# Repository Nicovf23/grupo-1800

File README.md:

# grupo-DON JULIO 
Proyecto Carrito Don Julio
El proyecto Carrito Don Julio consiste en el diseño y desarrollo de un vehículo eléctrico a escala, controlado por radio (RC), orientado al automodelismo de competición en pista para adultos. El objetivo es construir un vehículo desde cero, con un diseño enfocado en el alto rendimiento, la precisión de conducción y las exigencias técnicas de las carreras RC.
El proyecto contempla el diseño y fabricación de un chasis propio, la integración de un sistema de propulsión 100 % eléctrico, el desarrollo de circuitos electrónicos con componentes SMD (Surface-Mount Device) y la implementación de sistemas de control. Cada elemento será diseñado y seleccionado considerando factores como la velocidad, la aceleración, la estabilidad, la distribución del peso y la eficiencia energética.
Para el diseño y desarrollo se utilizarán herramientas especializadas como FreeCAD, para el modelado tridimensional del chasis y sus componentes mecánicos; KiCad, para el diseño de esquemáticos y placas de circuito impreso; Qucs-S, para la simulación y el análisis de circuitos electrónicos; y OpenModelica, para el modelado y la simulación de sistemas dinámicos.
El enfoque principal será desarrollar un vehículo competitivo para carreras en circuitos de pista, aplicando principios de ingeniería mecánica, electrónica, programación y microcontroladores. Se buscará optimizar cada componente para obtener un equilibrio entre potencia, control, estabilidad y rendimiento, mediante un proceso continuo de diseño, fabricación, pruebas y ajustes.

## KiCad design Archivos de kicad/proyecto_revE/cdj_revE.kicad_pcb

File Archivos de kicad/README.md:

# Carrito Don Julio: placa principal (KiCad)

## Revisión E (nueva, 26-11-2026): PRELIMINAR

> ⚠️ **REV E EN DESARROLLO.** Esquemático completo (ERC: 0 errores). PCB colocada y casi ruteada: DRC 0 errores, **73 conexiones sin rutear** todavía. **No mandar a fabricar.**

| | |
|---|---|
| Microcontrolador | **ESP32-S3RH2 soldado** (QFN56) + flash W25Q128JV 16 MB + cristal 40 MHz + antena U.FL |
| Alimentación | 6S → **LMR36510** (5.42 V) → OR con USB → **AP63203** (3.3 V) |
| Programación | USB-C de datos propio (el otro USB-C sigue siendo solo de carga) |
| Seguridad | Failsafe por hardware (monoestable 74LVC1G123 + interruptor de armado) |
| PCB | 125 × 95 mm, 4 capas JLC04161H-7628, In1 = GND sólido |
| Herramienta | **KiCad 10** (no abre en KiCad 9) |

| Carpeta | Contenido |
|---|---|
| `proyecto_revE/` | Proyecto KiCad 10: abrir `cdj_revE.kicad_pro` |
| `documentacion_revE/` | Esquemático PDF, BOM, GPIO, cálculos, auditoría, plan de pruebas, ERC/DRC, imágenes |
| `fabricacion_revE_PRELIMINAR/` | Gerbers, taladros, BOM, CPL, STEP. **Preliminares, no fabricar** |
| `../Documentación/Informe técnico Carrito Don Julio (rev E).pdf` | Informe completo para explicar y entregar |

La rev D (abajo) se conserva como respaldo.

---

## Revisión D

> ⚠️ **ESTADO: EN DESARROLLO. NO ES UNA VERSIÓN DE PRODUCCIÓN.**
> El ruteo está completo (DRC: 0 errores, 0 conexiones sin rutear), pero no mandar a fabricar todavía: faltan verificaciones físicas y una revisión del diseño (ver [AUDITORIA.md](AUDITORIA.md)).

**Revisión:** D, ruteo 3 (11 de noviembre de 2026)
**Herramienta:** KiCad 9.0
**Vehículo:** RC 1:7, 4WD, batería LiPo 6S (22.2 V nominal / 25.2 V cargada)

## Qué hace esta placa

| Bloque | Componentes principales |
|---|---|
| Microcontrolador | ESP32 DevKit V1 (DOIT, 30 pines) en zócalo |
| Sensor de movimiento | IMU LSM6DSL (I2C, dirección 0x6A) |
| Carga de batería por USB-C | CH224K (pide 20 V por PD) → BQ25756 (buck-boost 6S) |
| Monitoreo y balanceo de celdas | BQ76930 (6 celdas, por el cable de balanceo) |
| Alimentación 3.3 V | AP63203WU (componente recomendado por el profesor) |
| Luces | 2× BTS723GW (4 canales con diagnóstico) |
| Radio control | Entradas PWM ×3 + serie (CRSF/SBUS/iBUS), protegidas |
| Salidas | ESC y servo con buffer y habilitación |
| Protección | ESD5Z3.3T, SMF24CA/SMF26CA, SMF3.3, MBRA340T, fusible |

## Estructura de la carpeta

| Carpeta | Contenido |
|---|---|
| `proyecto_revD/` | Proyecto KiCad editable: esquemático, PCB, librería propia `CDJ` (símbolos y huellas) |
| `fabricacion_PRELIMINAR/` | Gerbers, taladros, BOM, posiciones (CPL) y modelo STEP. **Preliminares, no fabricar** |
| `documentacion/` | Esquemático en PDF, vista 3D, BOM clasificada (A/B/C), mapa de pines del DevKit, instrucciones y `EXPLICACION_PLACA.md` (qué hace cada componente y cada parte del PCB) |
| `reportes/` | Informes ERC, DRC y verificación de la netlist |
| `AUDITORIA.md` | Qué está verificado, qué no, y qué falta para producción |
| `NOTAS_DISENO.md` | Decisiones de diseño, supuestos y cálculos |

## Cómo abrir

1. Abrir `proyecto_revD/cdj_revD.kicad_pro` con KiCad 9.
2. La librería `CDJ` se carga sola desde la carpeta del proyecto (`sym-lib-table` y `fp-lib-table`).

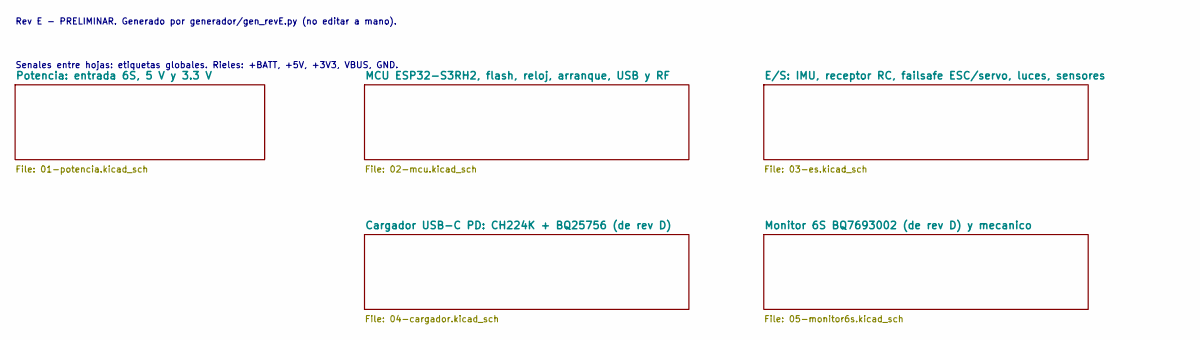
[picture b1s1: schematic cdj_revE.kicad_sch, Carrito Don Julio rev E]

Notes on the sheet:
Senales entre hojas: etiquetas globales. Rieles: +BATT, +5V, +3V3, VBUS, GND.
Rev E - PRELIMINAR. Generado por generador/gen_revE.py (no editar a mano).

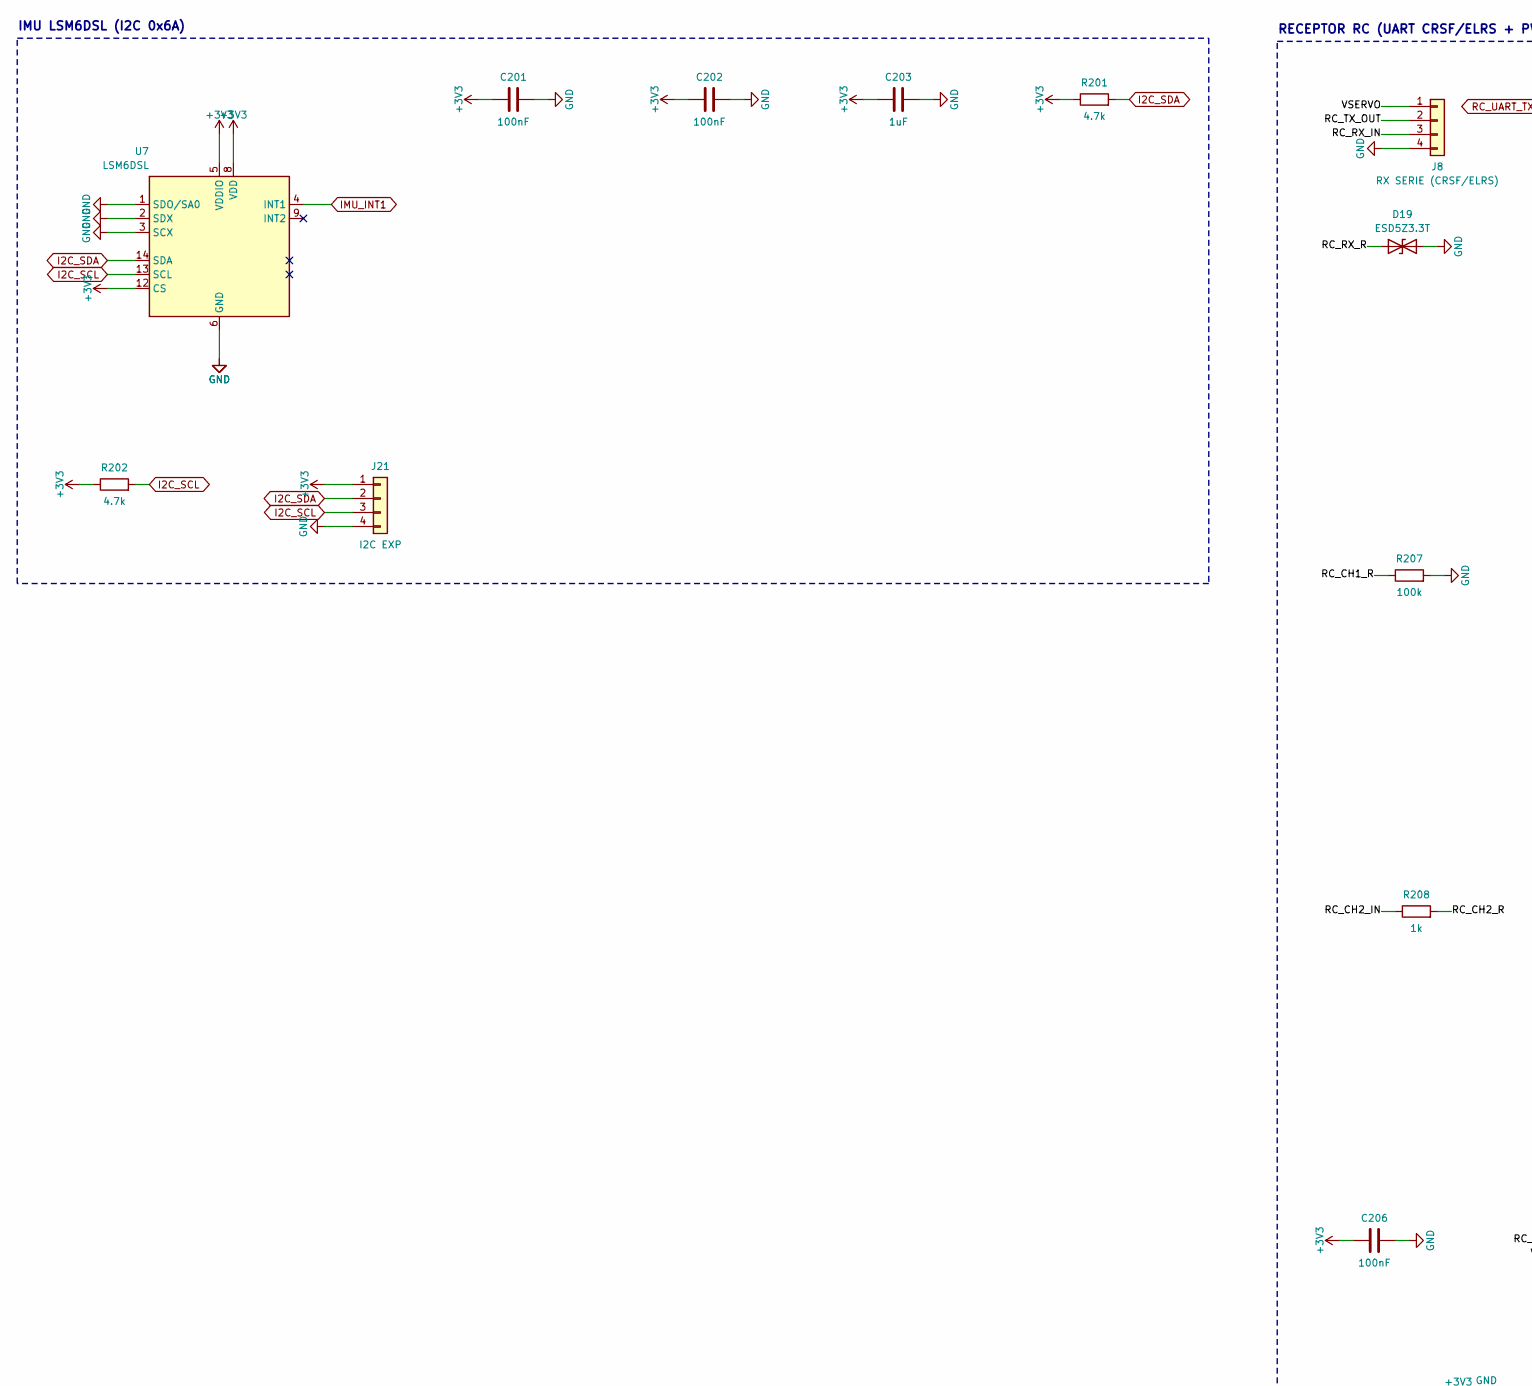
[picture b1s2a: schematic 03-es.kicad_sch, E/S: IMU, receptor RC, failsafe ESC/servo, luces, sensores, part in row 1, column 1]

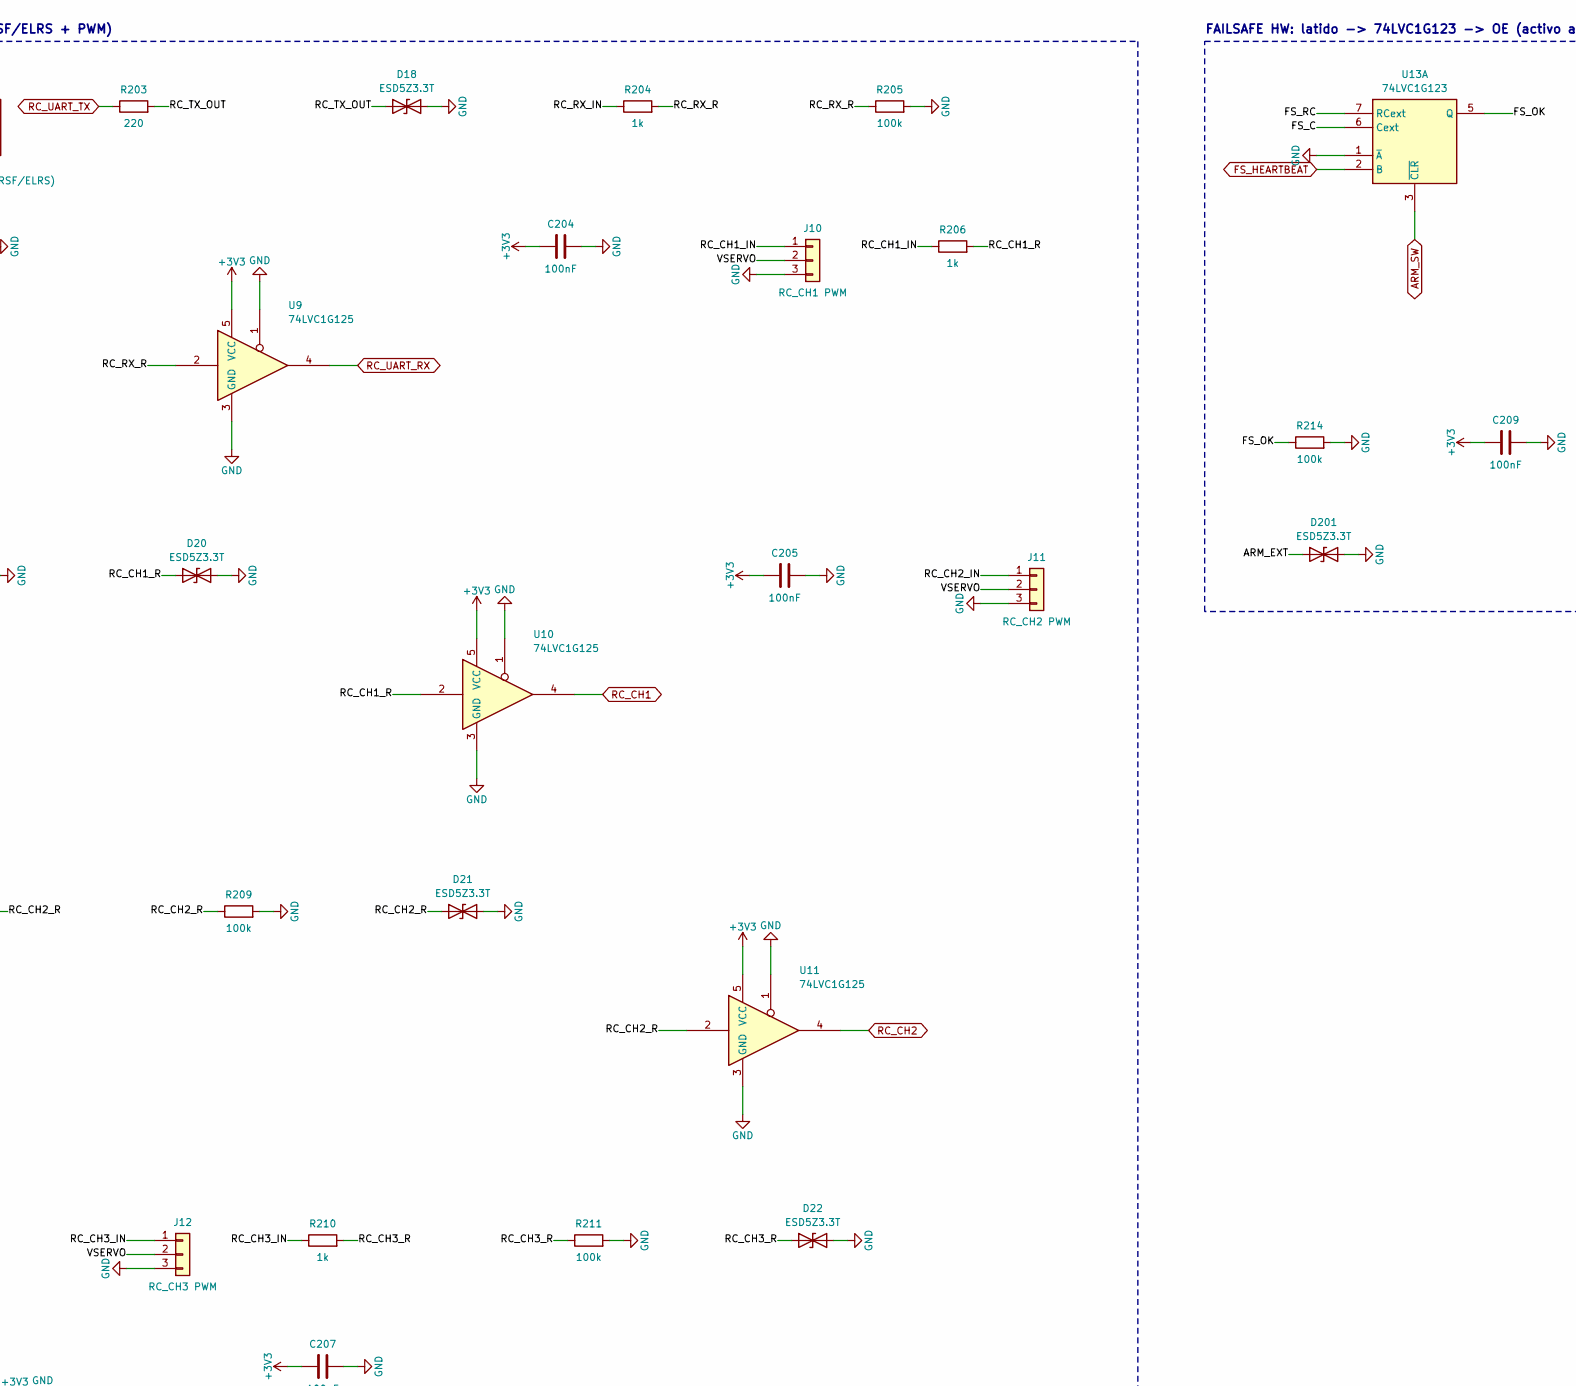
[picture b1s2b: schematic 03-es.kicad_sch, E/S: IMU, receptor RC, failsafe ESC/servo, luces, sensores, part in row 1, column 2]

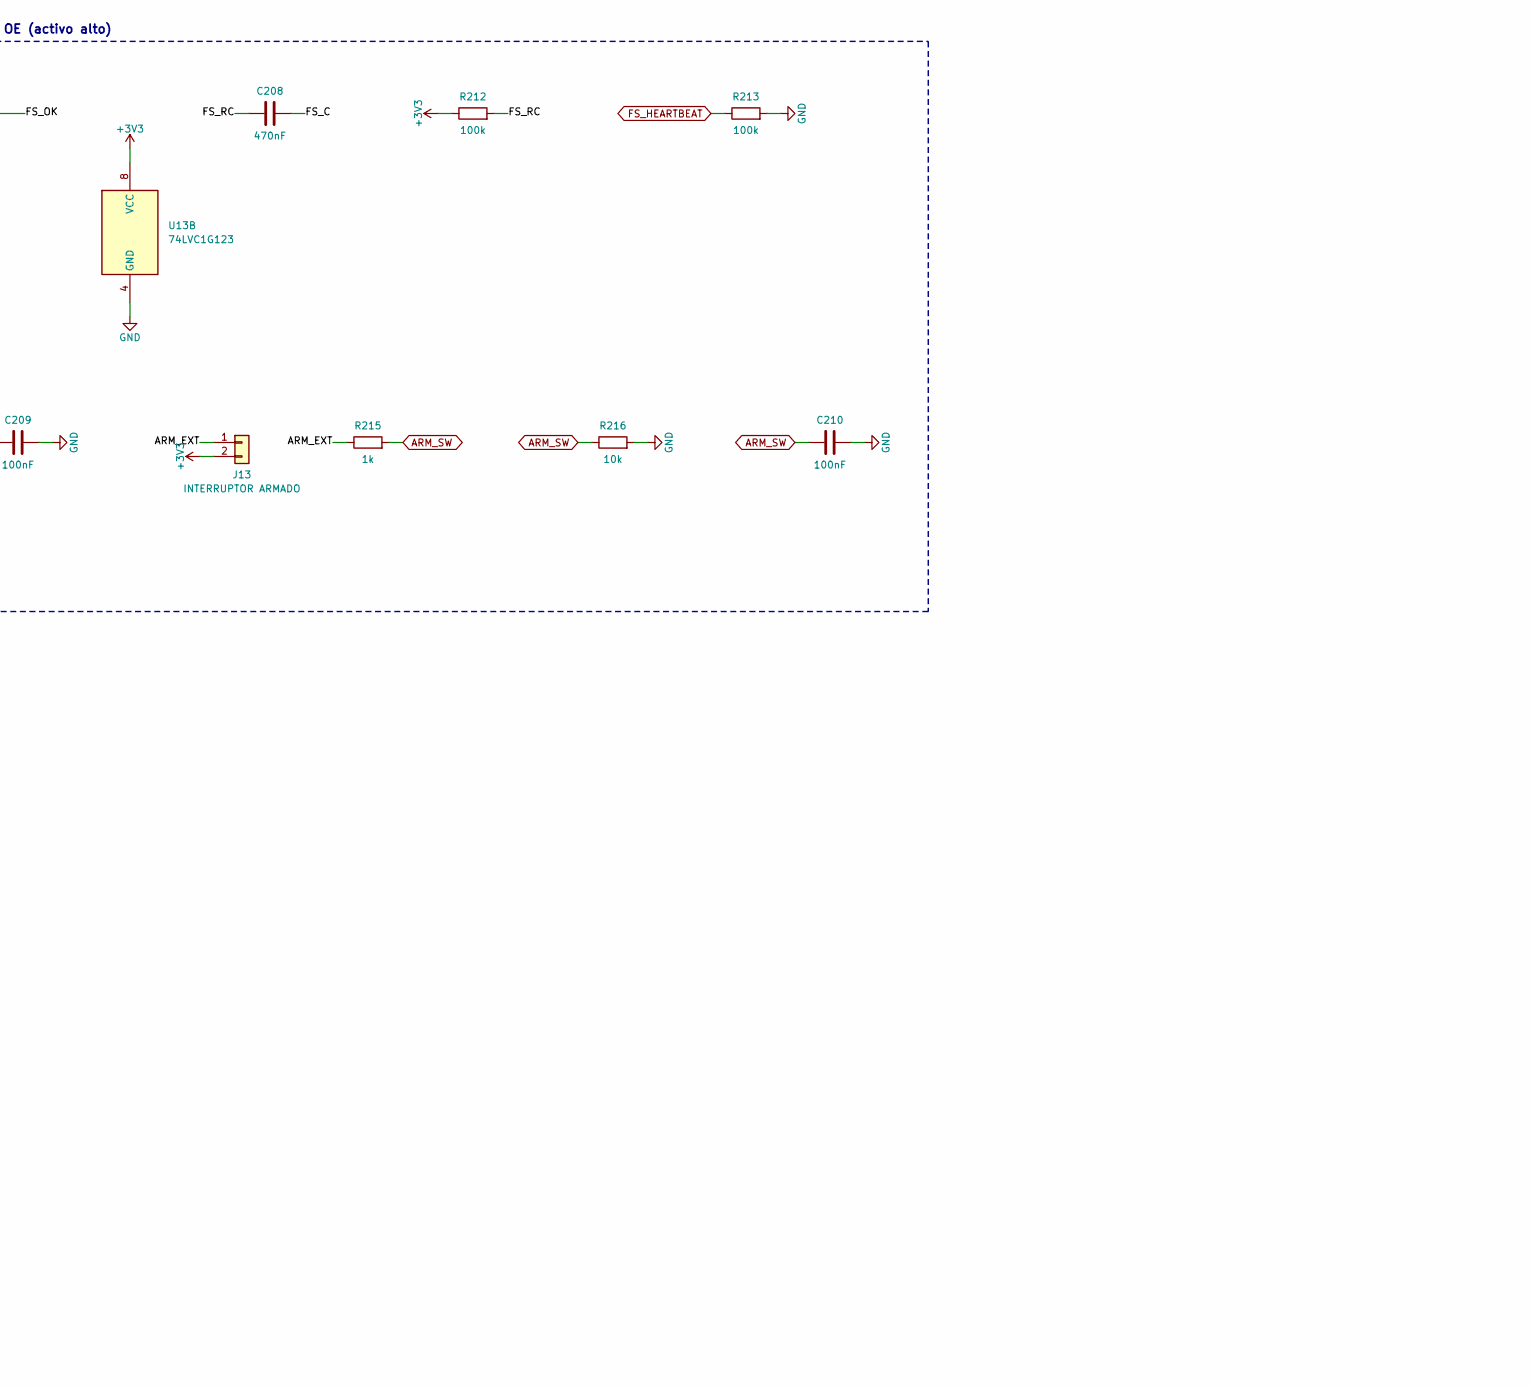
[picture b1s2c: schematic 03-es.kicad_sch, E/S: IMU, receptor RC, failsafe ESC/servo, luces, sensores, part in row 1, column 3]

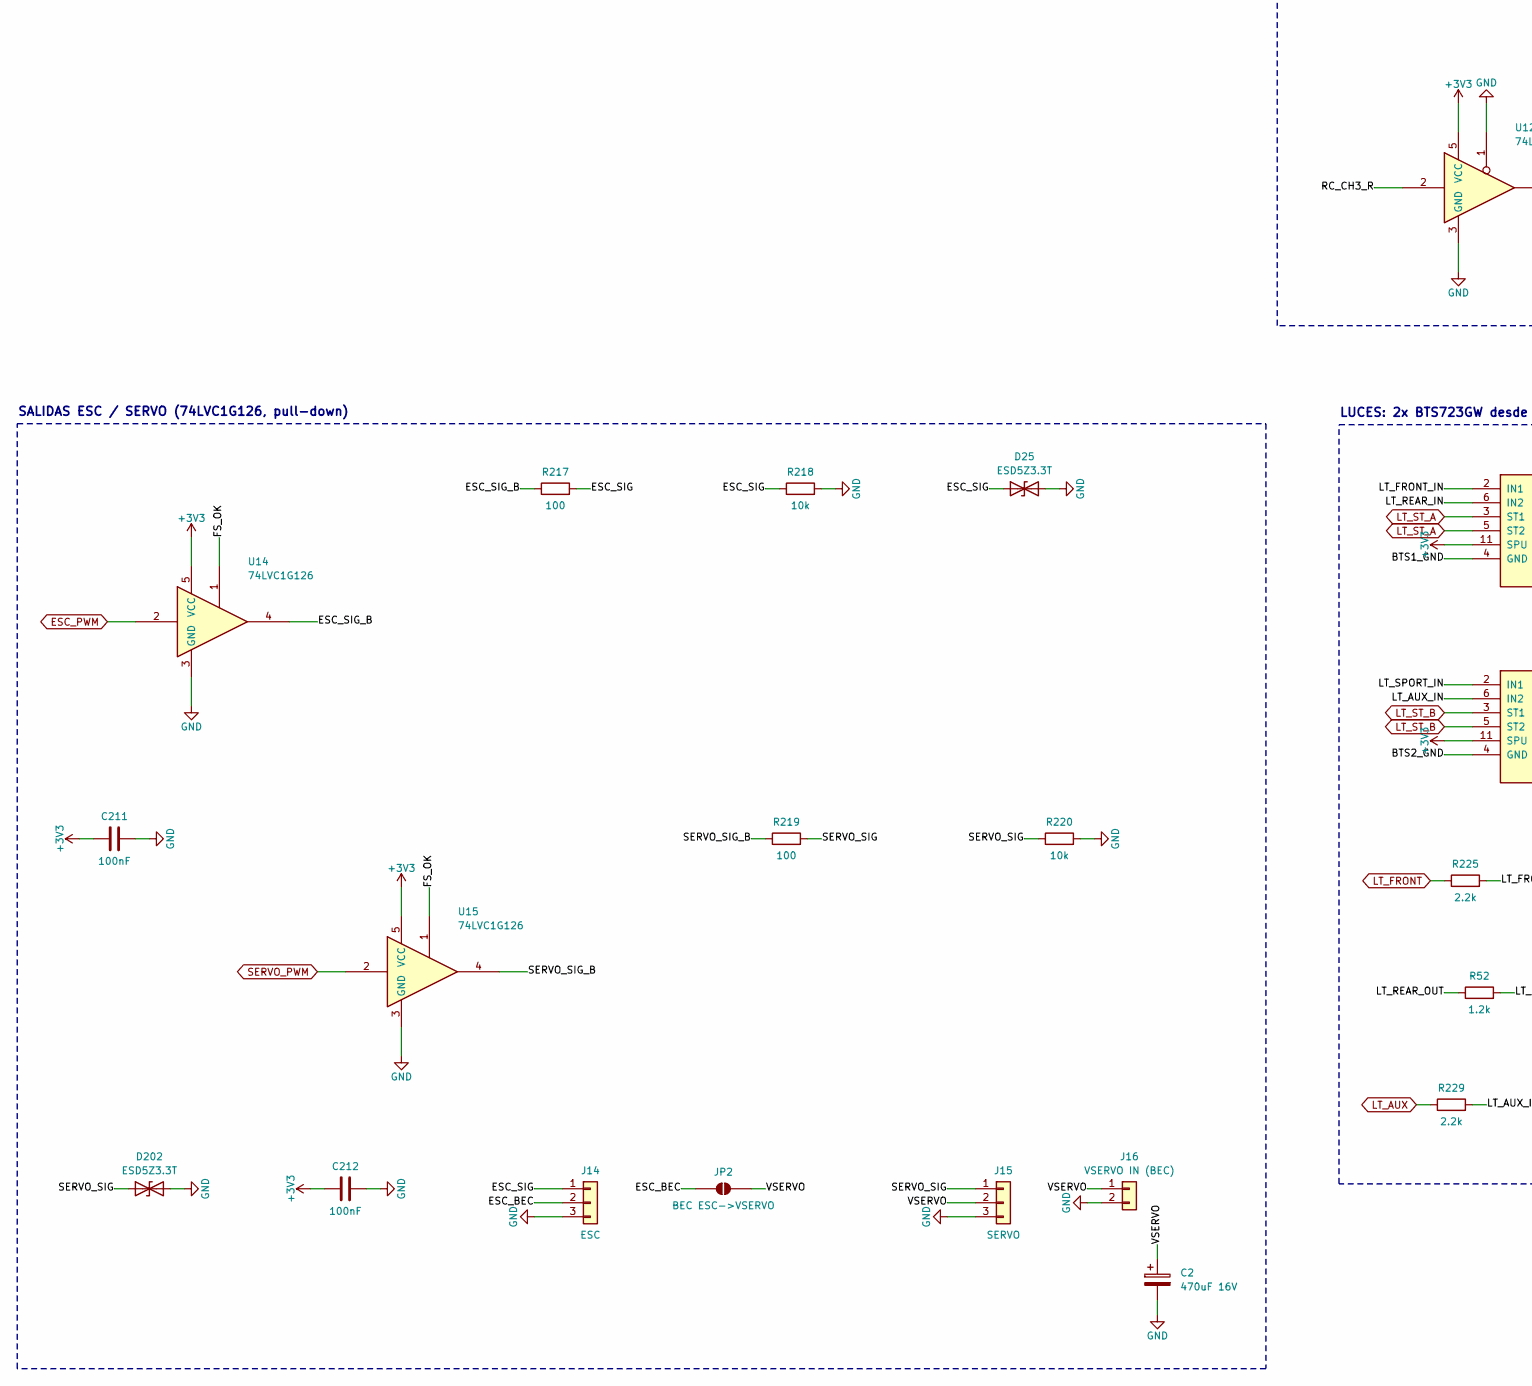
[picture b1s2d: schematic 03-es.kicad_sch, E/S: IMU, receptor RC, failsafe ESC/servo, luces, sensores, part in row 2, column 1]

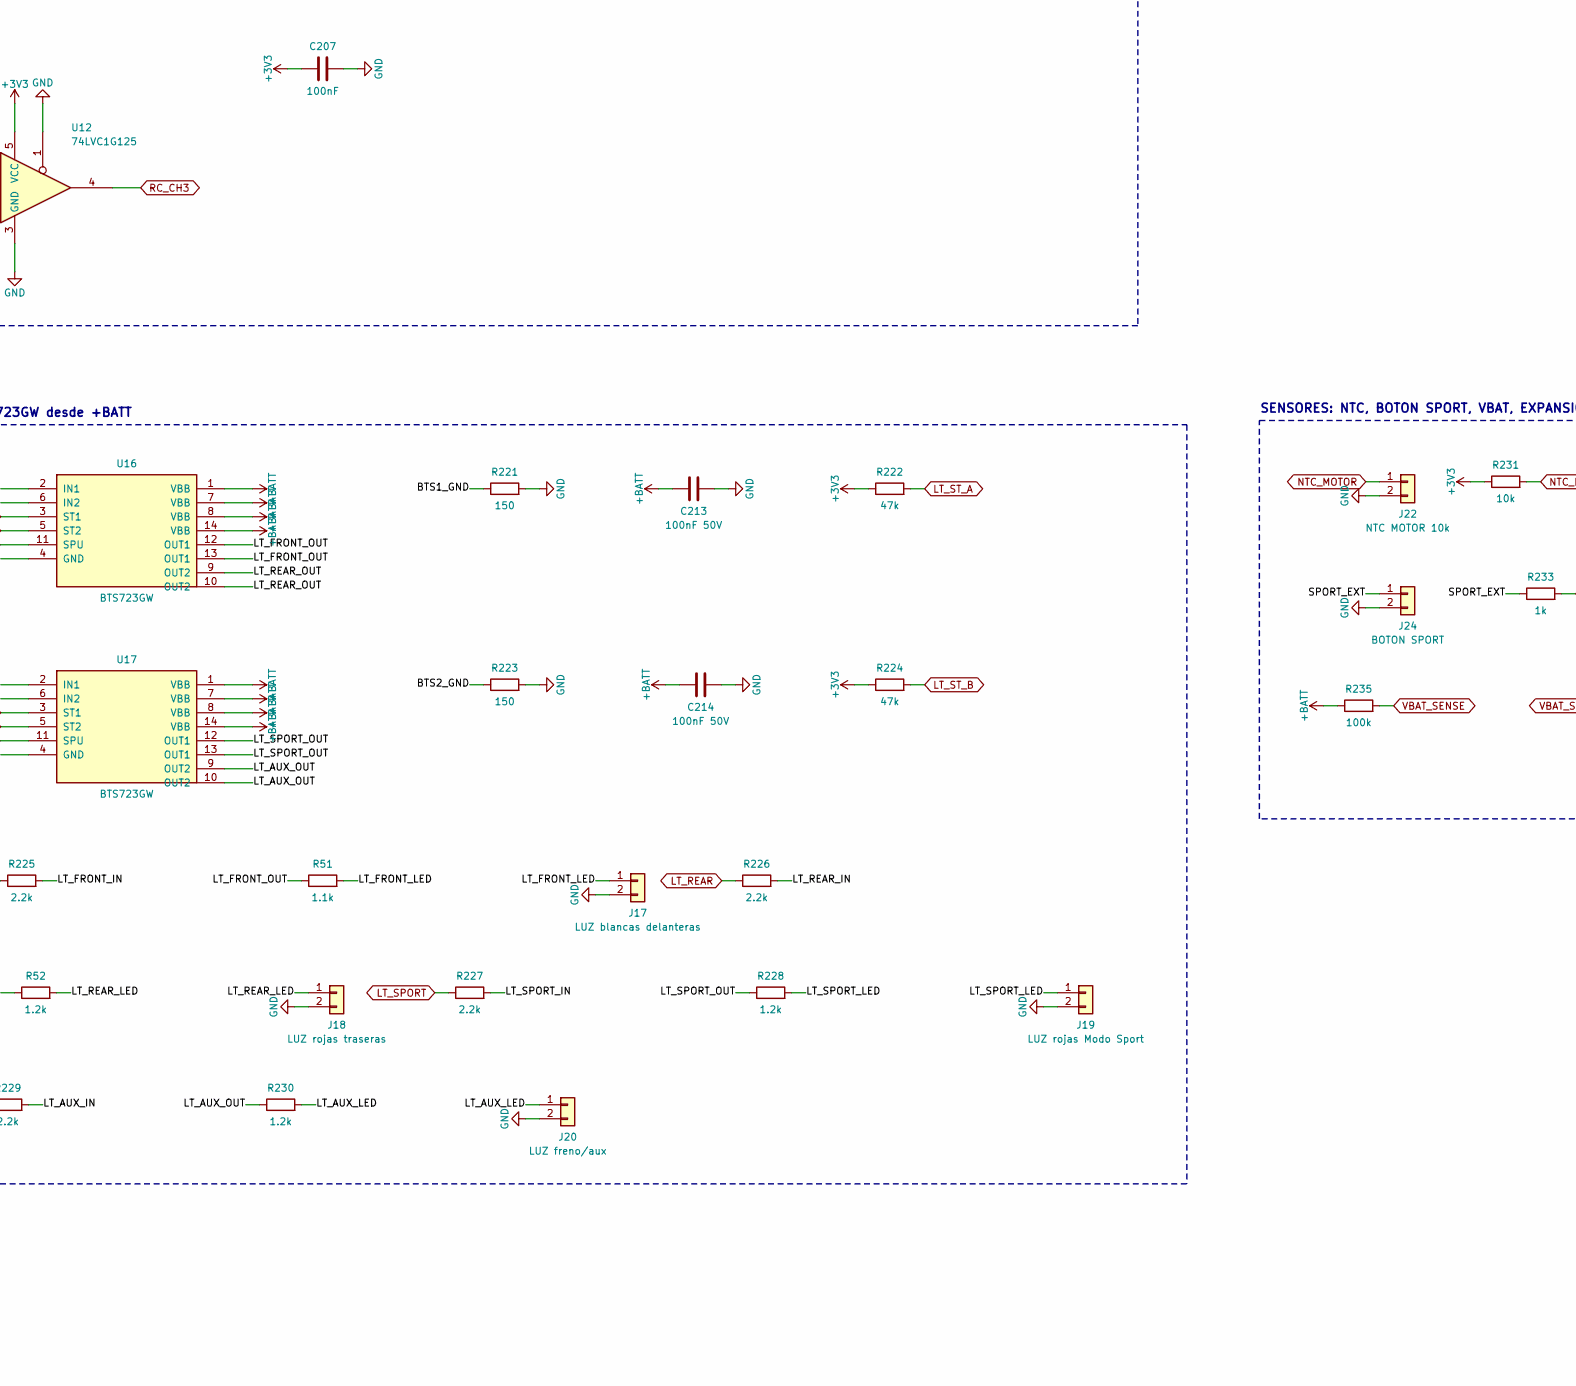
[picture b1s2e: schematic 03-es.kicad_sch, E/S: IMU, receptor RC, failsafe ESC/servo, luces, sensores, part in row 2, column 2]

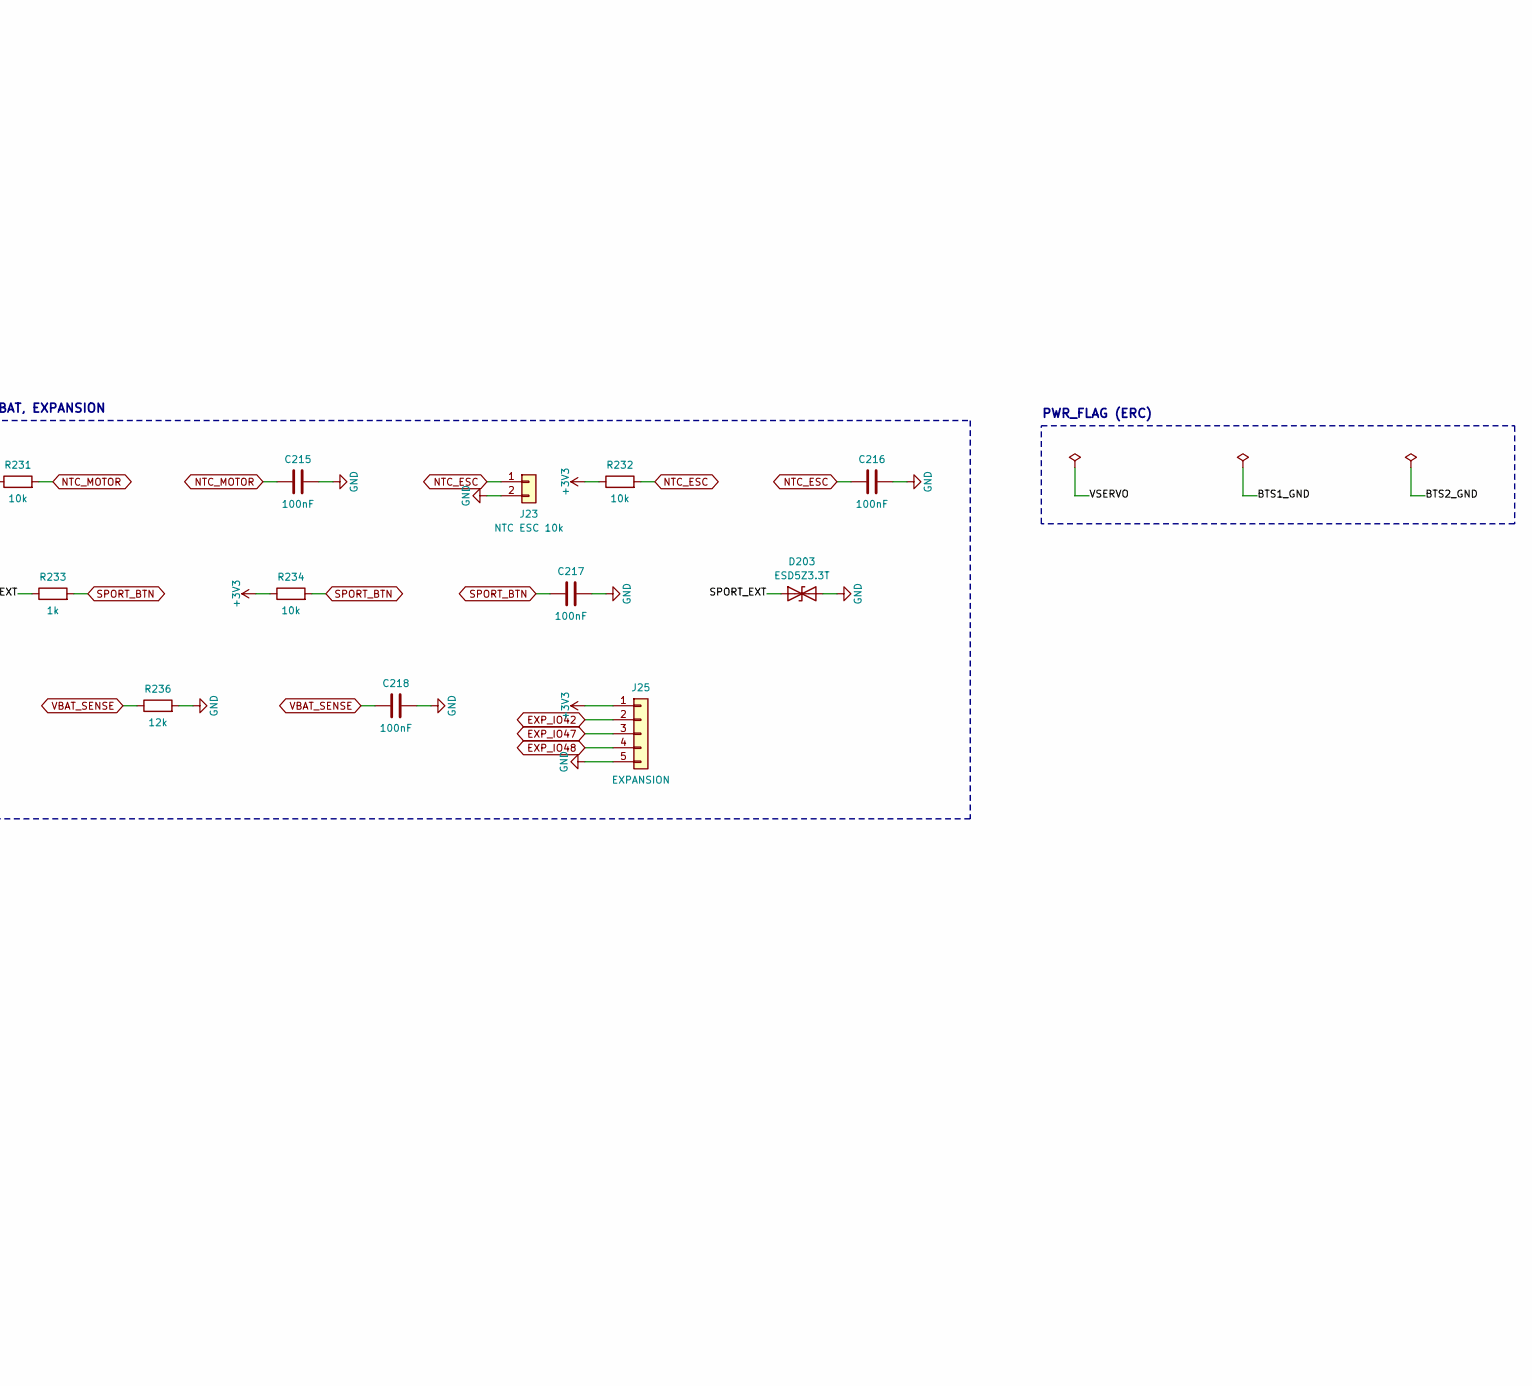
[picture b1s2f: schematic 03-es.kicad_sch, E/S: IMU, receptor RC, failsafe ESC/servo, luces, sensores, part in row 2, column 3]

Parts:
C2: 470uF 16V; CP_Elec_8x10.5; MPN Aluminio 470 uF / 16 V (profesor)
C201, C202, C204, C205, C206, C207, C209, C211, C212, C215, C216, C217, C218: 100nF; C_0402_1005Metric; MPN X7R 0402
C203: 1uF; C_0402_1005Metric; MPN X5R 0402
C208: 470nF; C_0603_1608Metric; MPN X7R 0603 (Cext; + en Rext/Cext)
C210: 100nF; C_0402_1005Metric; MPN X7R 0402 (antirrebote)
C213, C214: 100nF 50V; C_0603_1608Metric; MPN X7R 0603 50 V
D18, D19, D20, D21, D22, D25, D201, D202, D203: ESD5Z3.3T; D_SOD-523; MPN onsemi ESD5Z3.3T1G (profesor)
J8: RX SERIE (CRSF/ELRS); JST_PH_B4B-PH-K_1x04_P2.00mm_Vertical; MPN JST B4B-PH-K-S
J10: RC_CH1 PWM; PinHeader_1x03_P2.54mm_Vertical; MPN Header 1x03 2.54 mm
J11: RC_CH2 PWM; PinHeader_1x03_P2.54mm_Vertical; MPN Header 1x03 2.54 mm
J12: RC_CH3 PWM; PinHeader_1x03_P2.54mm_Vertical; MPN Header 1x03 2.54 mm
J13: INTERRUPTOR ARMADO; JST_PH_B2B-PH-K_1x02_P2.00mm_Vertical; MPN JST B2B-PH-K-S
J14: ESC; PinHeader_1x03_P2.54mm_Vertical; MPN Header 1x03 2.54 mm
J15: SERVO; PinHeader_1x03_P2.54mm_Vertical; MPN Header 1x03 2.54 mm
J16: VSERVO IN (BEC); AMASS_XT30PW-M_1x02_P2.50mm_Horizontal; MPN AMASS XT30PW-M
J17: LUZ blancas delanteras; JST_PH_B2B-PH-K_1x02_P2.00mm_Vertical; MPN JST B2B-PH-K-S
J18: LUZ rojas traseras; JST_PH_B2B-PH-K_1x02_P2.00mm_Vertical; MPN JST B2B-PH-K-S
J19: LUZ rojas Modo Sport; JST_PH_B2B-PH-K_1x02_P2.00mm_Vertical; MPN JST B2B-PH-K-S
J20: LUZ freno/aux; JST_PH_B2B-PH-K_1x02_P2.00mm_Vertical; MPN JST B2B-PH-K-S
J21: I2C EXP; JST_PH_B4B-PH-K_1x04_P2.00mm_Vertical; MPN JST B4B-PH-K-S
J22: NTC MOTOR 10k; JST_PH_B2B-PH-K_1x02_P2.00mm_Vertical; MPN JST B2B-PH-K-S
J23: NTC ESC 10k; JST_PH_B2B-PH-K_1x02_P2.00mm_Vertical; MPN JST B2B-PH-K-S
J24: BOTON SPORT; JST_PH_B2B-PH-K_1x02_P2.00mm_Vertical; MPN JST B2B-PH-K-S
J25: EXPANSION; JST_PH_B5B-PH-K_1x05_P2.00mm_Vertical; MPN JST B5B-PH-K-S
JP2: BEC ESC->VSERVO; SolderJumper-2_P1.3mm_Open_RoundedPad1.0x1.5mm; MPN Puente de soldadura (abierto)
R51: 1.1k; R_2512_6332Metric; MPN 2512 1 W (1 LED a 6S: 0.45 W)
R52, R228, R230: 1.2k; R_2512_6332Metric; MPN 2512 1 W (1 LED a 6S: 0.45 W)
R201, R202: 4.7k; R_0603_1608Metric; MPN 1 % 0603
R203: 220; R_0603_1608Metric; MPN 1 % 0603
R204, R206, R208, R210, R215, R233: 1k; R_0603_1608Metric; MPN 1 % 0603
R205, R207, R209, R211: 100k; R_0603_1608Metric; MPN 1 % 0603
R212: 100k; R_0603_1608Metric; MPN 1 % 0603 (Rext: tw ~ Rext x Cext ~ 47 m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
R213: 100k; R_0603_1608Metric; MPN 1 % 0603 (sin latido en reset)
R214: 100k; R_0603_1608Metric; MPN 1 % 0603 (salidas apagadas sin alimenta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
R216: 10k; R_0603_1608Metric; MPN 1 % 0603 (abierto = desarmado)
R217, R219: 100; R_0603_1608Metric; MPN 1 % 0603
R218, R220: 10k; R_0603_1608Metric; MPN 1 % 0603 (sin pulsos -> failsafe ESC)
R221, R223: 150; R_0603_1608Metric; MPN 1 % 0603 (GND lógico, datasheet)
R222, R224: 47k; R_0603_1608Metric; MPN 1 % 0603 (pull-up ST, verificar con dat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
R225, R226, R227, R229: 2.2k; R_0603_1608Metric; MPN 1 % 0603
R231, R232, R234: 10k; R_0603_1608Metric; MPN 1 % 0603
R235: 100k; R_0603_1608Metric; MPN 1 % 0603 (25.2 V -> 2.70 V)
R236: 12k; R_0603_1608Metric; MPN 1 % 0603
U7: LSM6DSL; LGA-14_3x2.5mm_P0.5mm_LayoutBorder3x4y; MPN ST LSM6DSLTR
U9, U10, U11, U12: 74LVC1G125; SOT-23-5; MPN TI SN74LVC1G125DBVR (entrada 5 V tolera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
U13: 74LVC1G123
U14, U15: 74LVC1G126; SOT-23-5; MPN TI SN74LVC1G126DBVR (OE activo alto)
U16, U17: BTS723GW; SOIC-14_3.9x8.7mm_P1.27mm; MPN Infineon BTS723GWXUMA1 (profesor)

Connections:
/E/S: IMU, receptor RC, failsafe ESC/servo, luces, sensores/ARM_EXT: D201.1 (A1), J13.1, R215.1
/E/S: IMU, receptor RC, failsafe ESC/servo, luces, sensores/ESC_BEC: J14.2, JP2.1 (A)
/E/S: IMU, receptor RC, failsafe ESC/servo, luces, sensores/ESC_SIG: D25.1 (A1), J14.1, R217.2, R218.1
/E/S: IMU, receptor RC, failsafe ESC/servo, luces, sensores/ESC_SIG_B: R217.1, U14.4
/E/S: IMU, receptor RC, failsafe ESC/servo, luces, sensores/FS_C: C208.2, U13.6 (Cext)
/E/S: IMU, receptor RC, failsafe ESC/servo, luces, sensores/FS_OK: R214.1, U13.5 (Q), U14.1, U15.1
/E/S: IMU, receptor RC, failsafe ESC/servo, luces, sensores/FS_RC: C208.1, R212.2, U13.7 (RCext)
/E/S: IMU, receptor RC, failsafe ESC/servo, luces, sensores/LT_AUX_IN: R229.2, U17.6 (IN2)
/E/S: IMU, receptor RC, failsafe ESC/servo, luces, sensores/LT_AUX_LED: J20.1, R230.2
/E/S: IMU, receptor RC, failsafe ESC/servo, luces, sensores/LT_AUX_OUT: R230.1, U17.9 (OUT2), U17.10 (OUT2)
/E/S: IMU, receptor RC, failsafe ESC/servo, luces, sensores/LT_FRONT_IN: R225.2, U16.2 (IN1)
/E/S: IMU, receptor RC, failsafe ESC/servo, luces, sensores/LT_FRONT_LED: J17.1, R51.2
/E/S: IMU, receptor RC, failsafe ESC/servo, luces, sensores/LT_FRONT_OUT: R51.1, U16.12 (OUT1), U16.13 (OUT1)
/E/S: IMU, receptor RC, failsafe ESC/servo, luces, sensores/LT_REAR_IN: R226.2, U16.6 (IN2)
/E/S: IMU, receptor RC, failsafe ESC/servo, luces, sensores/LT_REAR_LED: J18.1, R52.2
/E/S: IMU, receptor RC, failsafe ESC/servo, luces, sensores/LT_REAR_OUT: R52.1, U16.9 (OUT2), U16.10 (OUT2)
/E/S: IMU, receptor RC, failsafe ESC/servo, luces, sensores/LT_SPORT_IN: R227.2, U17.2 (IN1)
/E/S: IMU, receptor RC, failsafe ESC/servo, luces, sensores/LT_SPORT_LED: J19.1, R228.2
/E/S: IMU, receptor RC, failsafe ESC/servo, luces, sensores/LT_SPORT_OUT: R228.1, U17.12 (OUT1), U17.13 (OUT1)
/E/S: IMU, receptor RC, failsafe ESC/servo, luces, sensores/RC_CH1_IN: J10.1, R206.1
/E/S: IMU, receptor RC, failsafe ESC/servo, luces, sensores/RC_CH1_R: D20.1 (A1), R206.2, R207.1, U10.2
/E/S: IMU, receptor RC, failsafe ESC/servo, luces, sensores/RC_CH2_IN: J11.1, R208.1
/E/S: IMU, receptor RC, failsafe ESC/servo, luces, sensores/RC_CH2_R: D21.1 (A1), R208.2, R209.1, U11.2
/E/S: IMU, receptor RC, failsafe ESC/servo, luces, sensores/RC_CH3_IN: J12.1, R210.1
/E/S: IMU, receptor RC, failsafe ESC/servo, luces, sensores/RC_CH3_R: D22.1 (A1), R210.2, R211.1, U12.2
/E/S: IMU, receptor RC, failsafe ESC/servo, luces, sensores/RC_RX_IN: J8.3, R204.1
/E/S: IMU, receptor RC, failsafe ESC/servo, luces, sensores/RC_RX_R: D19.1 (A1), R204.2, R205.1, U9.2
/E/S: IMU, receptor RC, failsafe ESC/servo, luces, sensores/RC_TX_OUT: D18.1 (A1), J8.2, R203.2
/E/S: IMU, receptor RC, failsafe ESC/servo, luces, sensores/SERVO_SIG: D202.1 (A1), J15.1, R219.2, R220.1
/E/S: IMU, receptor RC, failsafe ESC/servo, luces, sensores/SERVO_SIG_B: R219.1, U15.4
/E/S: IMU, receptor RC, failsafe ESC/servo, luces, sensores/SPORT_EXT: D203.1 (A1), J24.1, R233.1
ARM_SW: C210.1, R215.2, R216.1, U13.3 (~CLR); also elsewhere on the board
ESC_PWM: U14.2; also elsewhere on the board
EXP_IO42: J25.2; also elsewhere on the board
EXP_IO47: J25.3; also elsewhere on the board
EXP_IO48: J25.4; also elsewhere on the board
FS_HEARTBEAT: R213.1, U13.2 (B); also elsewhere on the board
I2C_SCL: J21.3, R202.2, U7.13 (SCL); also elsewhere on the board
I2C_SDA: J21.2, R201.2, U7.14 (SDA); also elsewhere on the board
IMU_INT1: U7.4 (INT1); also elsewhere on the board
LT_AUX: R229.1; also elsewhere on the board
LT_FRONT: R225.1; also elsewhere on the board
LT_REAR: R226.1; also elsewhere on the board
LT_SPORT: R227.1; also elsewhere on the board
LT_ST_A: R222.2, U16.3 (ST1), U16.5 (ST2); also elsewhere on the board
LT_ST_B: R224.2, U17.3 (ST1), U17.5 (ST2); also elsewhere on the board
NTC_ESC: C216.1, J23.1, R232.2; also elsewhere on the board
NTC_MOTOR: C215.1, J22.1, R231.2; also elsewhere on the board
RC_CH1: U10.4; also elsewhere on the board
RC_CH2: U11.4; also elsewhere on the board
RC_CH3: U12.4; also elsewhere on the board
RC_UART_RX: U9.4; also elsewhere on the board
RC_UART_TX: R203.1; also elsewhere on the board
SERVO_PWM: U15.2; also elsewhere on the board
SPORT_BTN: C217.1, R233.2, R234.2; also elsewhere on the board
VBAT_SENSE: C218.1, R235.2, R236.1; also elsewhere on the board

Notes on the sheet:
IMU LSM6DSL (I2C 0x6A)
FAILSAFE HW: latido -> 74LVC1G123 -> OE (activo alto)
PWR_FLAG (ERC)
LUCES: 2x BTS723GW desde +BATT
RECEPTOR RC (UART CRSF/ELRS + PWM)
SENSORES: NTC, BOTON SPORT, VBAT, EXPANSION
SALIDAS ESC / SERVO (74LVC1G126, pull-down)
